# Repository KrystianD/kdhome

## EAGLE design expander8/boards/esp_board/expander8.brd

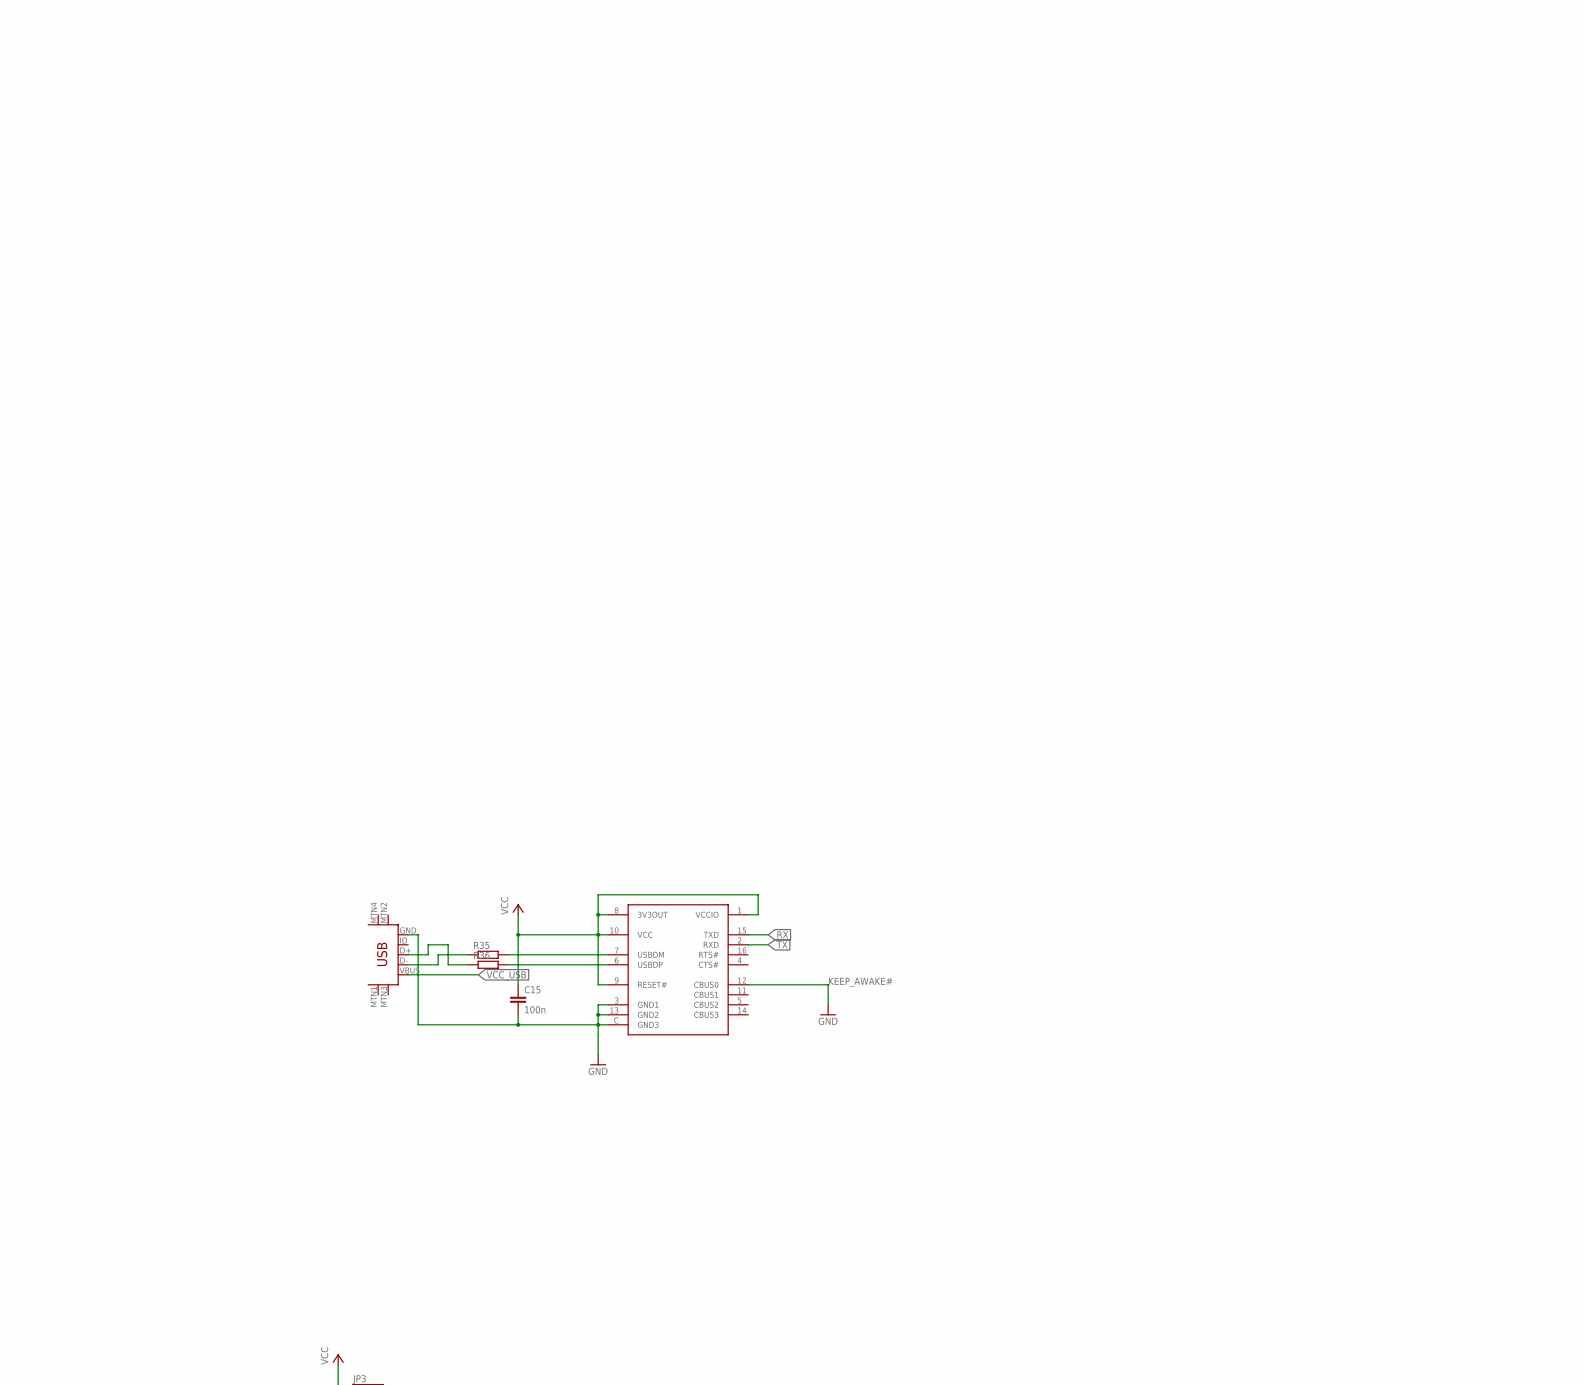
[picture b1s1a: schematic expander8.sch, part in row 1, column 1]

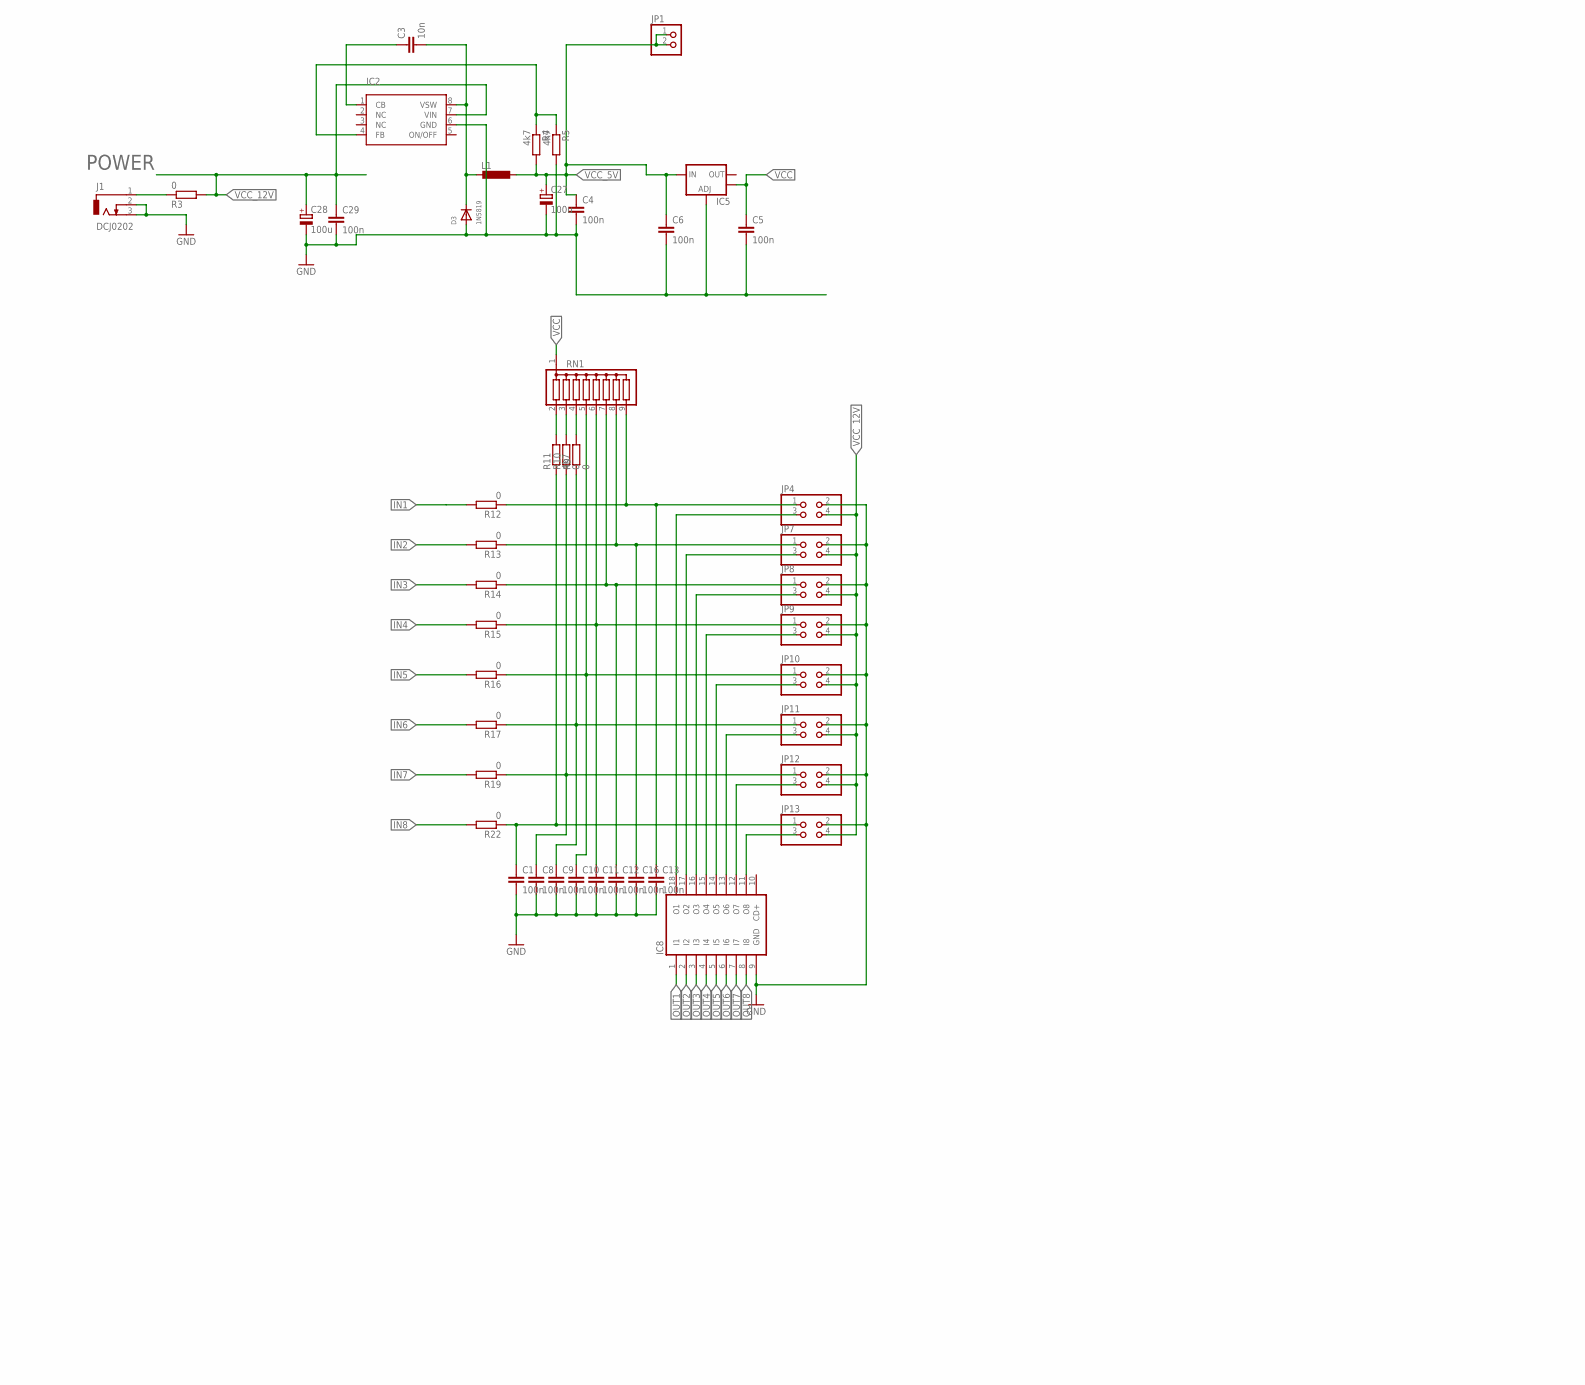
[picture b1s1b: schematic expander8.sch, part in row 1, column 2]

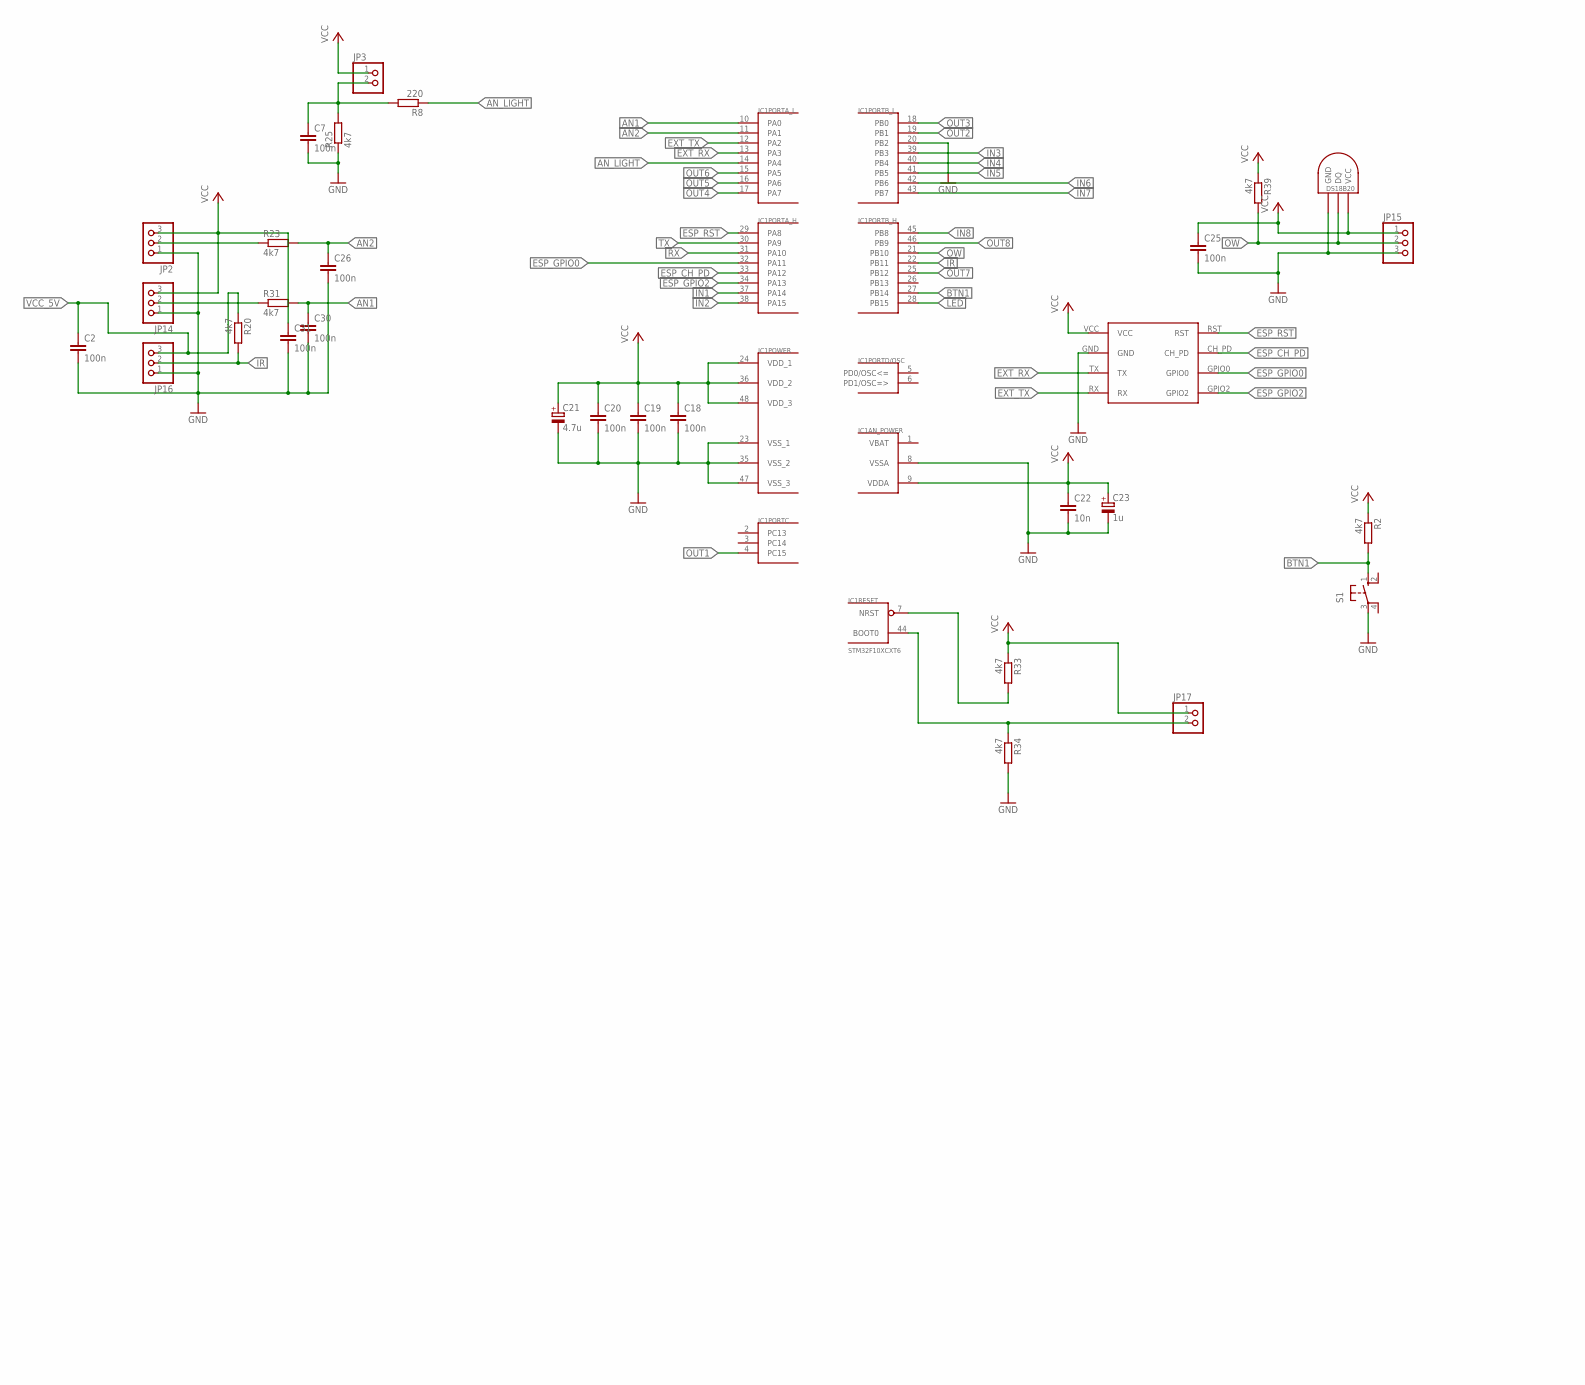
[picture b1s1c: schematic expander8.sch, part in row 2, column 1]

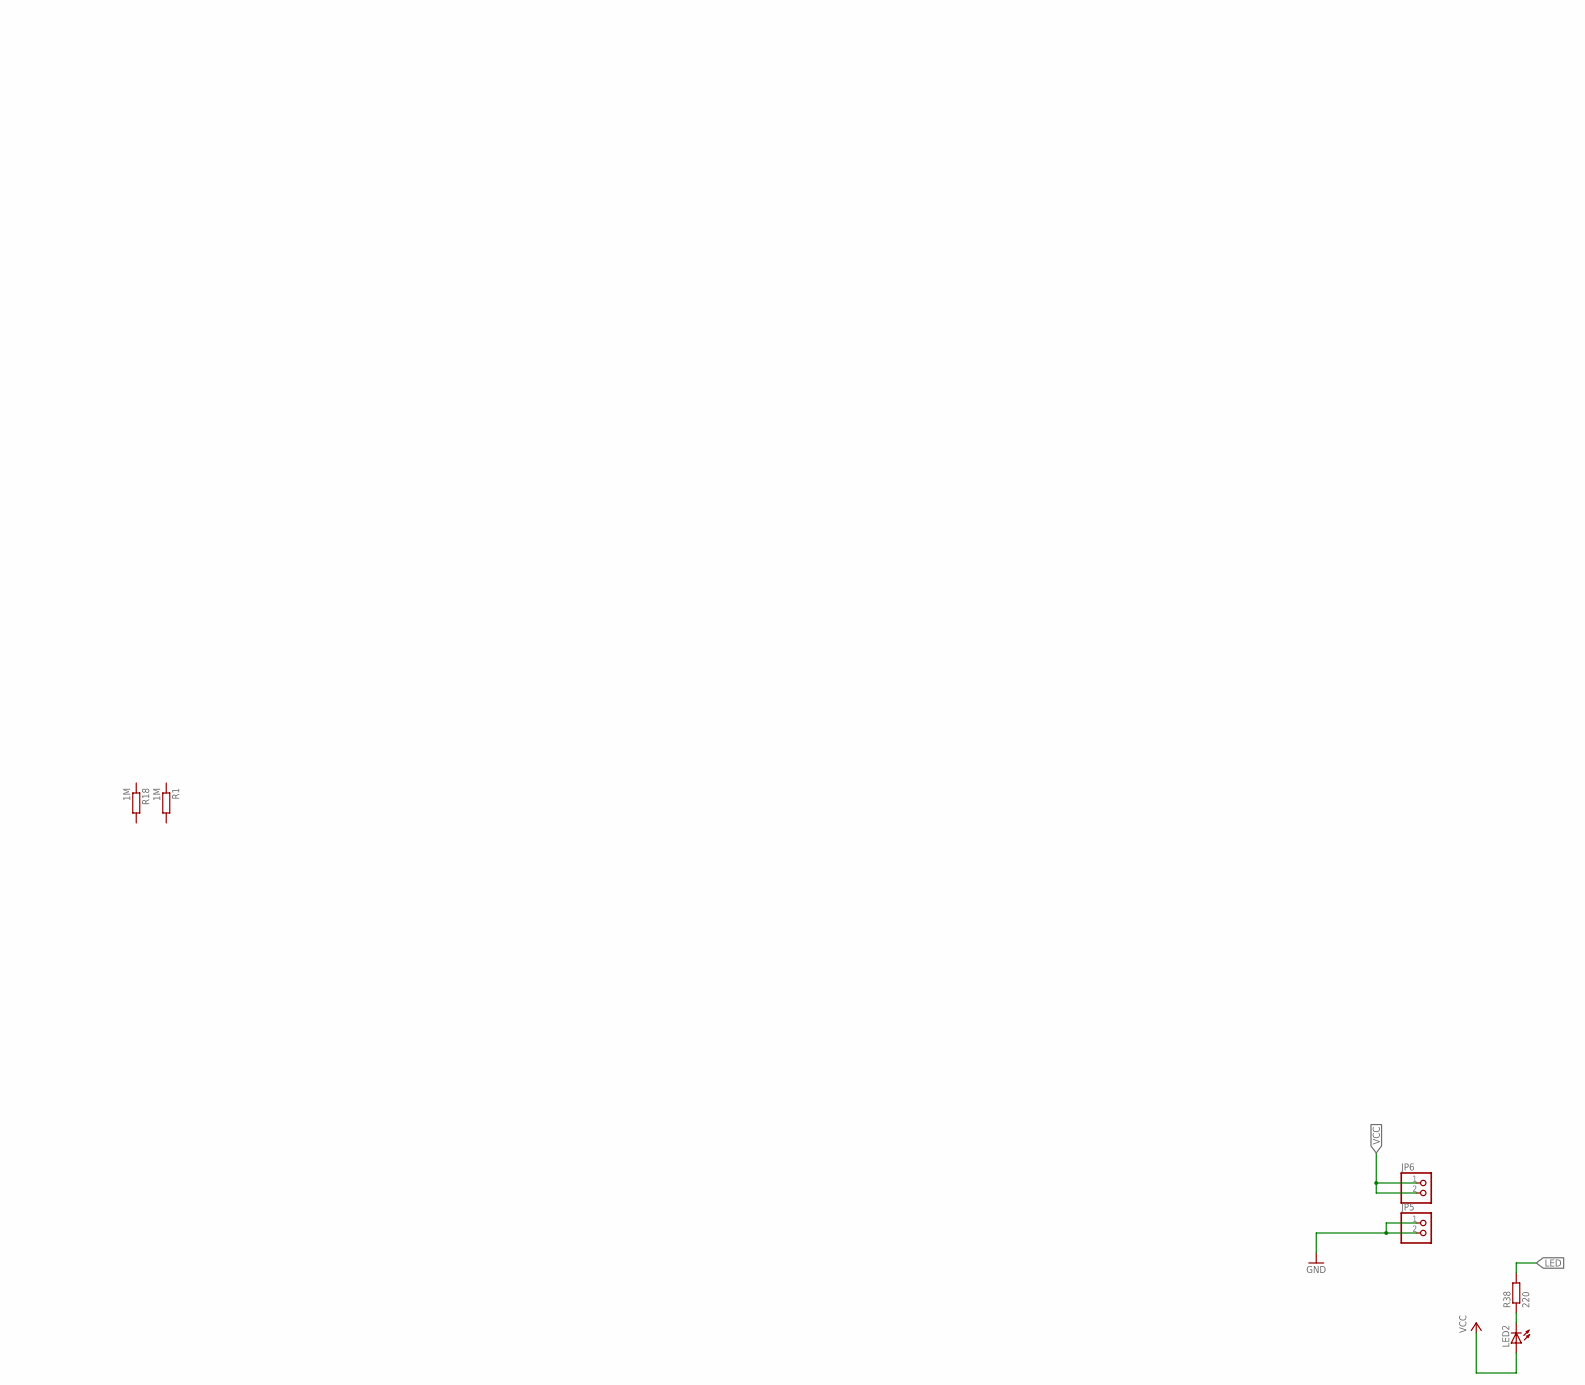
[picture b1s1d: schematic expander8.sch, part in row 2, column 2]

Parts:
C1, C2, C4, C5, C6, C7, C8, C9, C10, C11, C12, C13, C15, C16, C18, C19, C20, C25, C26, C29, C30: 100n; C0805
C3: 10n; C1206
C21: 4.7u; E2,5-5
C22: 10n; C0805
C23: 1u; E2,5-5
C27, C28: 100u; E2,5-7
C31: 100n; C1206
D3: 1N5819; SMADIODE
IC1: STM32F10XCXT6; TQFP48
IC2: LM2674; SO8
IC5: V_REG_LM1117SOT223; SOT223
IC8: ULN2803AD; SO18W
J1: DCJ0202
JP1, JP17: PINHD-1X2_2.54; 1X02
JP2, JP14, JP15, JP16: PINHD-1X3; 1X03
JP3, JP5, JP6: PINHD-1X2; 1X02
JP4, JP7, JP8, JP9, JP10, JP11, JP12, JP13: PINHD-2X2/90; 2X02/90
L1: L-EU0207/2V; 0207/2V
LED2: LEDCHIPLED_0805; CHIPLED_0805
R1, R18: 1M; R1206
R2, R4, R5, R11, R20, R23, R25, R33, R34, R39: 4k7; R0805
R3: 0; M1206
R8: 220; R1206
R9, R10, R12, R13, R14, R15, R16, R17, R19, R22: 0; R0805
R31: 4k7; R1206
R35: R-EU_R1206; R1206
R36: R-EU_R0805; R0805
R38: 220; R0805
RN1: G08R; SIL9
S1: 10-XX; B3F-10XX
U$1: ESP8266
U$2: USB-MINIB-5PIN; USB-MINIB
U$3: FT230XQ
U$4: DS1820TO92; DS1820

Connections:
AN1: C30.1, IC1.10 (PA0), R31.2
AN2: C26.1, IC1.11 (PA1), R23.2
AN_LIGHT: IC1.14 (PA4), R8.1
AN_LIGHT2: C7.1, JP3.2, R8.2, R25.2
BTN1: IC1.27 (PB14), R2.2, S1.1 (S)
ESP_CH_PD: IC1.33 (PA12), U$1.CH_PD
ESP_GPIO0: IC1.32 (PA11), U$1.GPIO0
ESP_GPIO2: IC1.34 (PA13), U$1.GPIO2
ESP_RST: IC1.29 (PA8), U$1.RST
EXT_RX: IC1.13 (PA3), U$1.TX
EXT_TX: IC1.12 (PA2), U$1.RX
GND: C1.2, C2.2, C4.2, C5.2, C6.2, C7.2, C8.2, C9.2, C10.2, C11.2, C12.2, C13.2, C15.2, C16.2, C18.2, C19.2, C20.2, C21.-, C22.2, C23.-, C25.2, C26.2, C27.-, C28.-, C29.2, C30.2, C31.2, D3.A, IC1.8 (VSSA), IC1.20 (PB2), IC1.23 (VSS_1), IC1.35 (VSS_2), IC1.47 (VSS_3), IC2.6 (GND), IC5.1 (ADJ), IC8.9 (GND), J1.2, J1.3, JP2.1, JP4.2, JP5.1, JP5.2, JP7.2, JP8.2, JP9.2, JP10.2, JP11.2, JP12.2, JP13.2, JP14.1, JP15.3, JP16.1, R5.2, R25.1, R34.2, S1.3, U$1.GND, U$2.GND, U$3.3 (GND1), U$3.12 (CBUS0), U$3.13 (GND2), U$3.C (GND3), U$4.GND
IN1: IC1.37 (PA14), R12.2
IN1_: C13.1, JP4.1, R12.1, RN1.9
IN2: IC1.38 (PA15), R13.2
IN2_: C16.1, JP7.1, R13.1, RN1.8
IN3: IC1.39 (PB3), R14.2
IN3_: C12.1, JP8.1, R14.1, RN1.7
IN4: IC1.40 (PB4), R15.2
IN4_: C11.1, JP9.1, R15.1, RN1.6
IN5: IC1.41 (PB5), R16.2
IN5_: C10.1, JP10.1, R16.1, RN1.5
IN6: IC1.42 (PB6), R17.2
IN6_: C9.1, JP11.1, R9.1, R17.1
IN7: IC1.43 (PB7), R19.2
IN7_: C8.1, JP12.1, R10.1, R19.1
IN8: IC1.45 (PB8), R22.2
IN8_: C1.1, JP13.1, R11.1, R22.1
IR: IC1.22 (PB11), JP16.2, R20.2
LED: IC1.28 (PB15), R38.2
unnamed: C3.2, D3.C, IC2.8 (VSW), L1.2
unnamed: IC2.4 (FB), R4.1, R5.1
unnamed: IC8.18 (O1), JP4.3
unnamed: IC8.17 (O2), JP7.3
unnamed: C3.1, IC2.1 (CB)
unnamed: J1.1, R3.1
unnamed: IC8.16 (O3), JP8.3
unnamed: R9.2, RN1.4
unnamed: IC8.15 (O4), JP9.3
unnamed: R10.2, RN1.3
unnamed: R11.2, RN1.2
unnamed: IC8.14 (O5), JP10.3
unnamed: IC8.13 (O6), JP11.3
unnamed: IC8.12 (O7), JP12.3
unnamed: LED2.C, R38.1
unnamed: IC8.11 (O8), JP13.3
unnamed: JP2.2, R23.1
unnamed: JP14.2, R31.1
unnamed: R35.1, U$2.D-
unnamed: R35.2, U$3.7 (USBDM)
unnamed: R36.2, U$3.6 (USBDP)
unnamed: R36.1, U$2.D+
unnamed: IC1.44 (BOOT0), JP17.2, R34.1
OUT1: IC1.4 (PC15), IC8.1 (I1)
OUT2: IC1.19 (PB1), IC8.2 (I2)
OUT3: IC1.18 (PB0), IC8.3 (I3)
OUT4: IC1.17 (PA7), IC8.4 (I4)
OUT5: IC1.16 (PA6), IC8.5 (I5)
OUT6: IC1.15 (PA5), IC8.6 (I6)
OUT7: IC1.25 (PB12), IC8.7 (I7)
OUT8: IC1.46 (PB9), IC8.8 (I8)
OW: IC1.21 (PB10), JP15.2, R39.2, U$4.DQ
RST1: IC1.7 (NRST), R33.2
RX: IC1.31 (PA10), U$3.15 (TXD)
TX: IC1.30 (PA9), U$3.2 (RXD)
VBAT: IC1.1 (VBAT)
VCC: C5.1, C15.1, C18.1, C19.1, C20.1, C21.+, C22.1, C23.+, C25.1, C31.1, IC1.9 (VDDA), IC1.24 (VDD_1), IC1.36 (VDD_2), IC1.48 (VDD_3), IC5.4 (OUT), JP2.3, JP3.1, JP6.1, JP6.2, JP14.3, JP15.1, JP17.1, LED2.A, R2.1, R33.1, R39.1, RN1.1, U$1.VCC, U$3.1 (VCCIO), U$3.8 (3V3OUT), U$3.9 (RESET#), U$3.10 (VCC), U$4.VDD (VCC)
VCC_5V: C2.1, C4.1, C6.1, C27.+, IC5.3 (IN), JP1.1, JP1.2, JP16.3, L1.1, R4.2, R20.1
VCC_12V: C28.+, C29.1, IC2.7 (VIN), JP4.4, JP7.4, JP8.4, JP9.4, JP10.4, JP11.4, JP12.4, JP13.4, R3.2
VCC_USB: U$2.VBUS

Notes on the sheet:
POWER
KEEP_AWAKE#

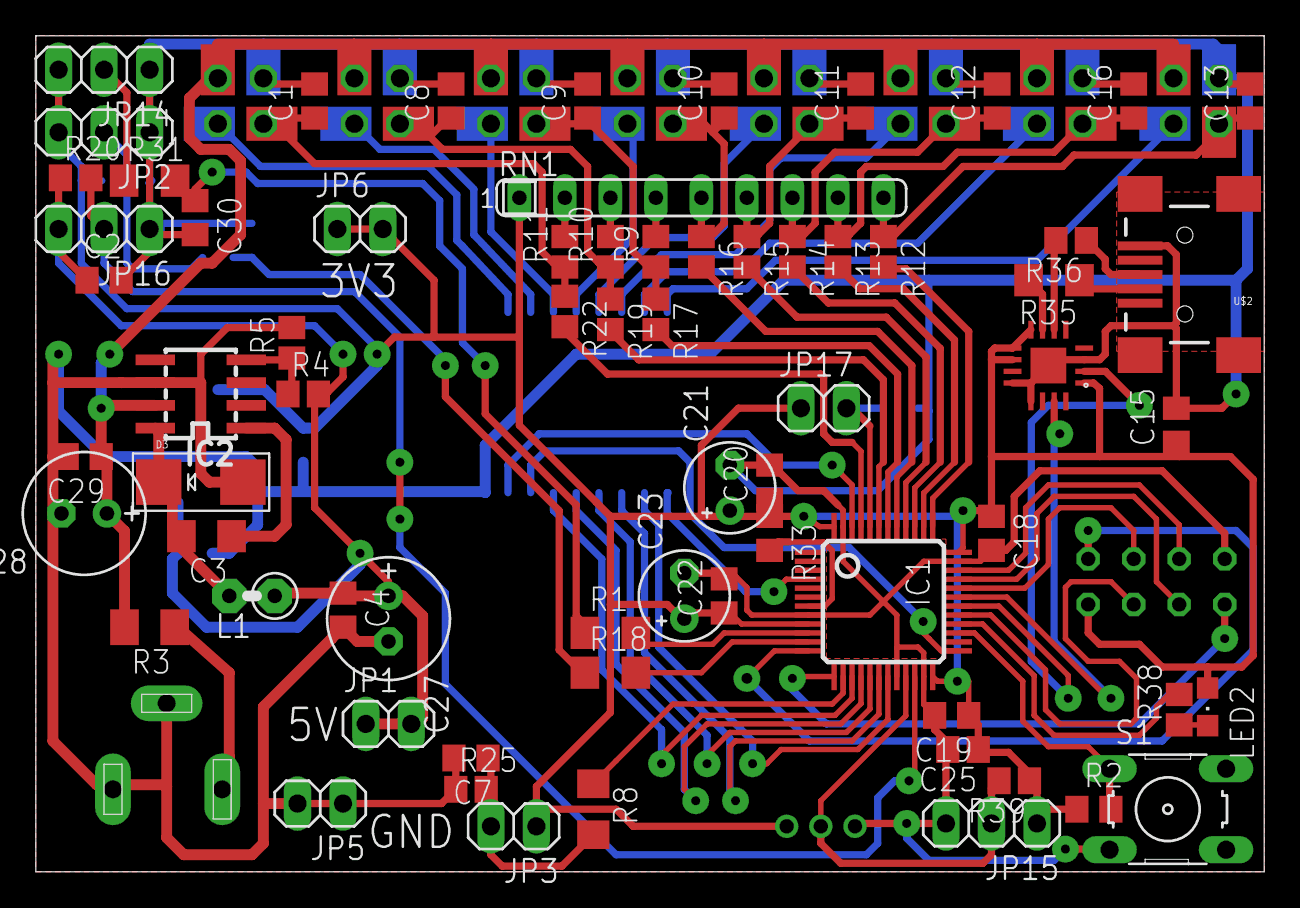
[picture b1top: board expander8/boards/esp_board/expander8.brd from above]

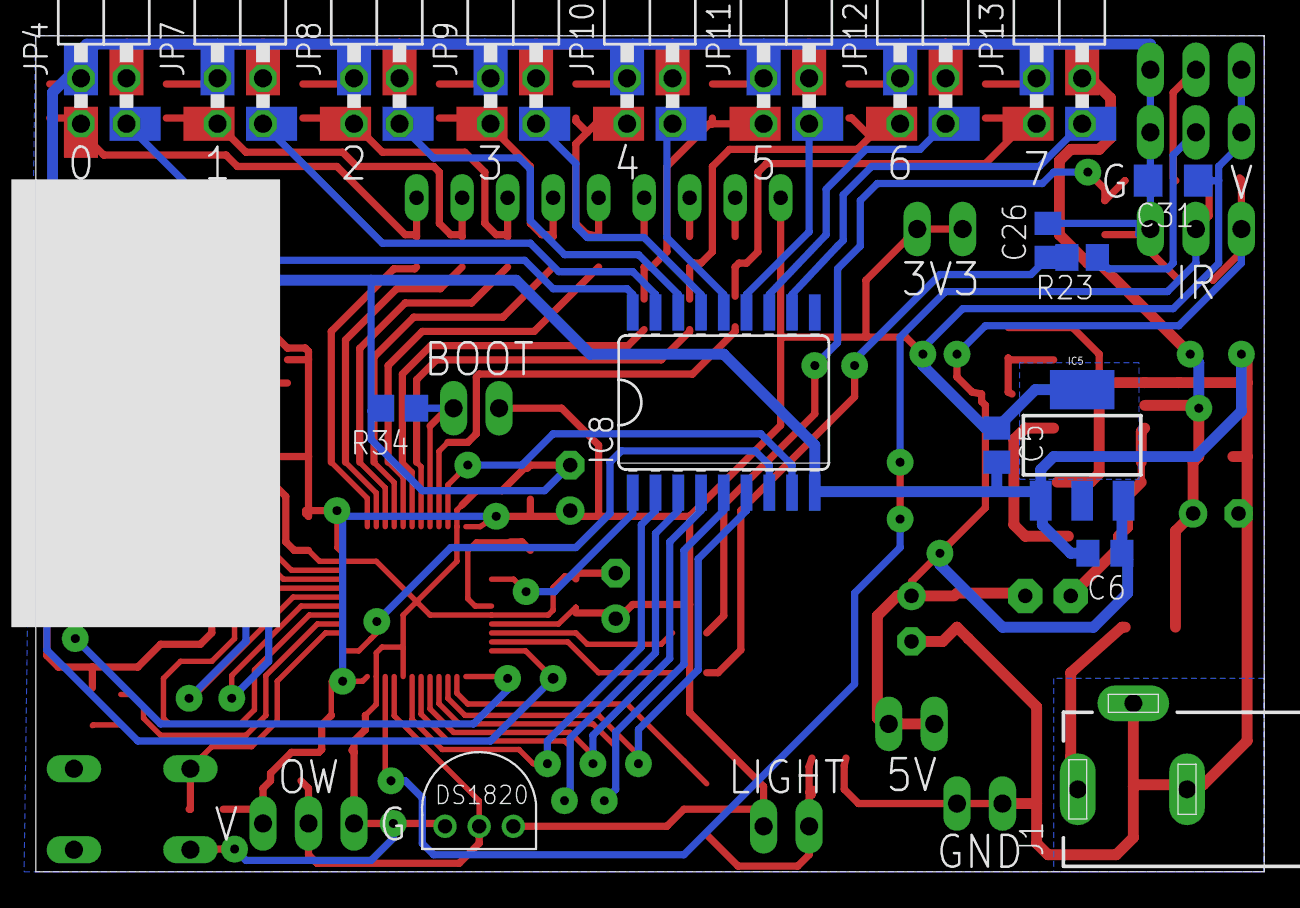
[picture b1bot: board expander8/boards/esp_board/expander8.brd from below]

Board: 2 copper layers, 68.6 x 46.7 mm, 87 parts (19 on the bottom side), 68 nets.

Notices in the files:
parts and their libraries:
SparkFun: Licensing: CC v3.0 Share-Alike You are welcome to use this library for commercial purposes.
